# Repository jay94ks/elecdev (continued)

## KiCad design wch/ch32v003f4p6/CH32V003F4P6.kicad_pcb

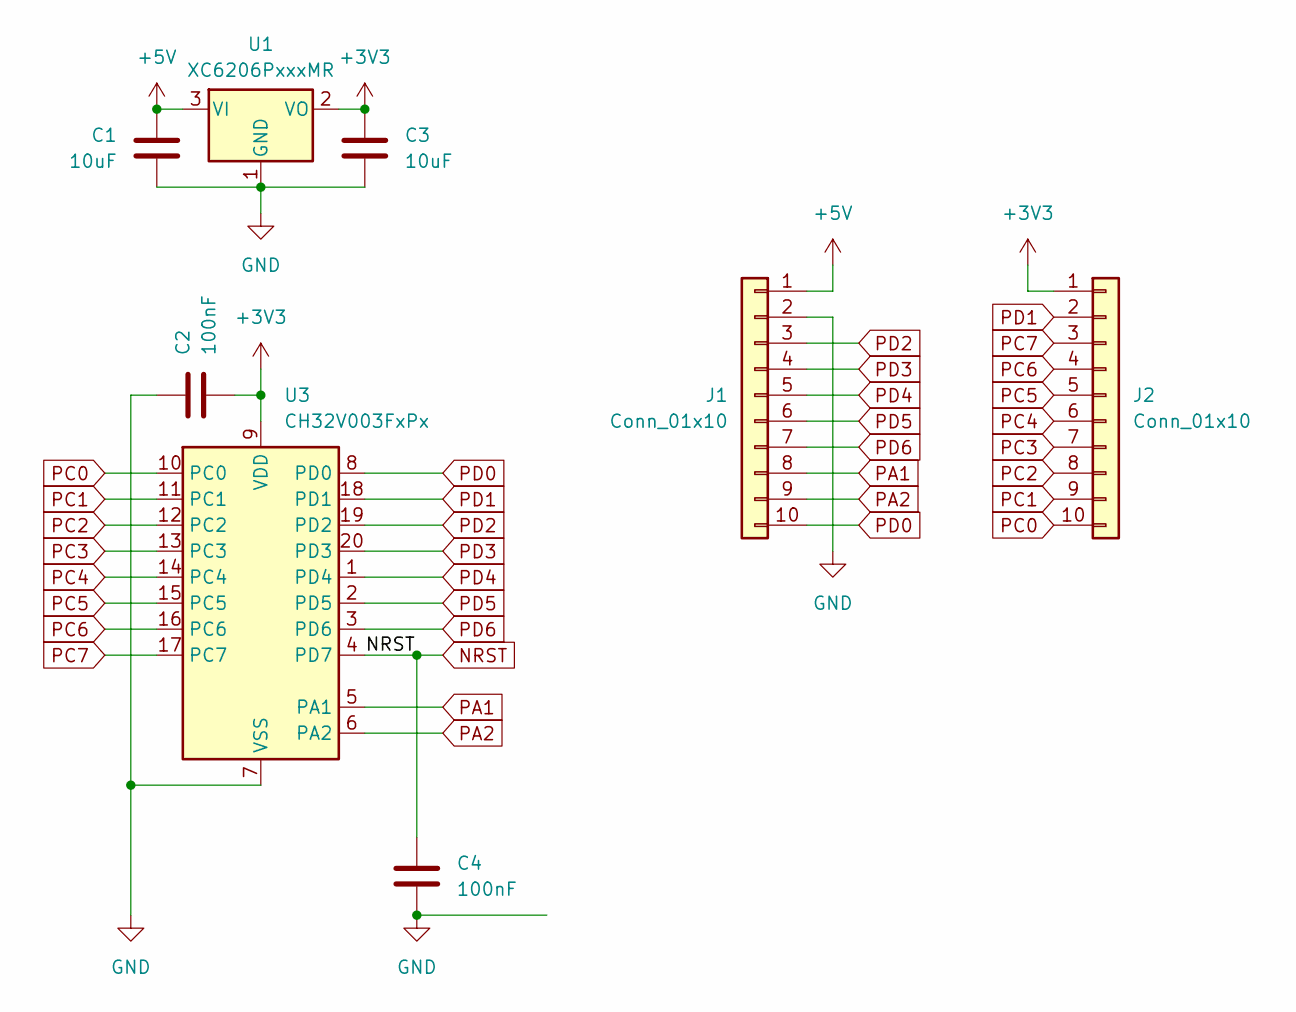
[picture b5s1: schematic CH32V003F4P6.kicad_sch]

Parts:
C1, C3: 10uF; C_0603_1608Metric
C2, C4: 100nF; C_0603_1608Metric
J1, J2: Conn_01x10; PinHeader_1x10_P2.54mm_Vertical
U1: XC6206PxxxMR; SOT-23-3
U3: CH32V003FxPx; TSSOP-20_4.4x6.5mm_P0.65mm

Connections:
+3V3: C2.2, C3.1, J2.1, U1.2 (VO), U3.9 (VDD)
+5V: C1.1, J1.1, U1.3 (VI)
GND: C1.2, C2.1, C3.2, C4.2, J1.2, U1.1 (GND), U3.7 (VSS)
NRST: C4.1, U3.4 (PD7)
PA1: J1.8, U3.5 (PA1)
PA2: J1.9, U3.6 (PA2)
PC0: J2.10, U3.10 (PC0)
PC1: J2.9, U3.11 (PC1)
PC2: J2.8, U3.12 (PC2)
PC3: J2.7, U3.13 (PC3)
PC4: J2.6, U3.14 (PC4)
PC5: J2.5, U3.15 (PC5)
PC6: J2.4, U3.16 (PC6)
PC7: J2.3, U3.17 (PC7)
PD0: J1.10, U3.8 (PD0)
PD1: J2.2, U3.18 (PD1)
PD2: J1.3, U3.19 (PD2)
PD3: J1.4, U3.20 (PD3)
PD4: J1.5, U3.1 (PD4)
PD5: J1.6, U3.2 (PD5)
PD6: J1.7, U3.3 (PD6)

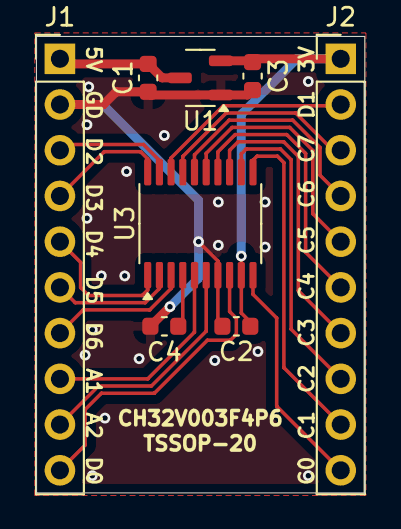
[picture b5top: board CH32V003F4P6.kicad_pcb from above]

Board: 2 copper layers, 18.2 x 25.4 mm, 8 parts (0 on the bottom side), 21 nets.

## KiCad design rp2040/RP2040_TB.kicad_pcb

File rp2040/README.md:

# RP2040.
ARM® Cortex®-M0+ Dual-core, 32bit, QFN-56.<br />
Features: 133 MHz max, 256kB SRAM, `UART` x2, `SPI` x2, `I2C` x2, `PWM` x 16 channel.<br/>
Board Size: -.<br />
Price: about -.

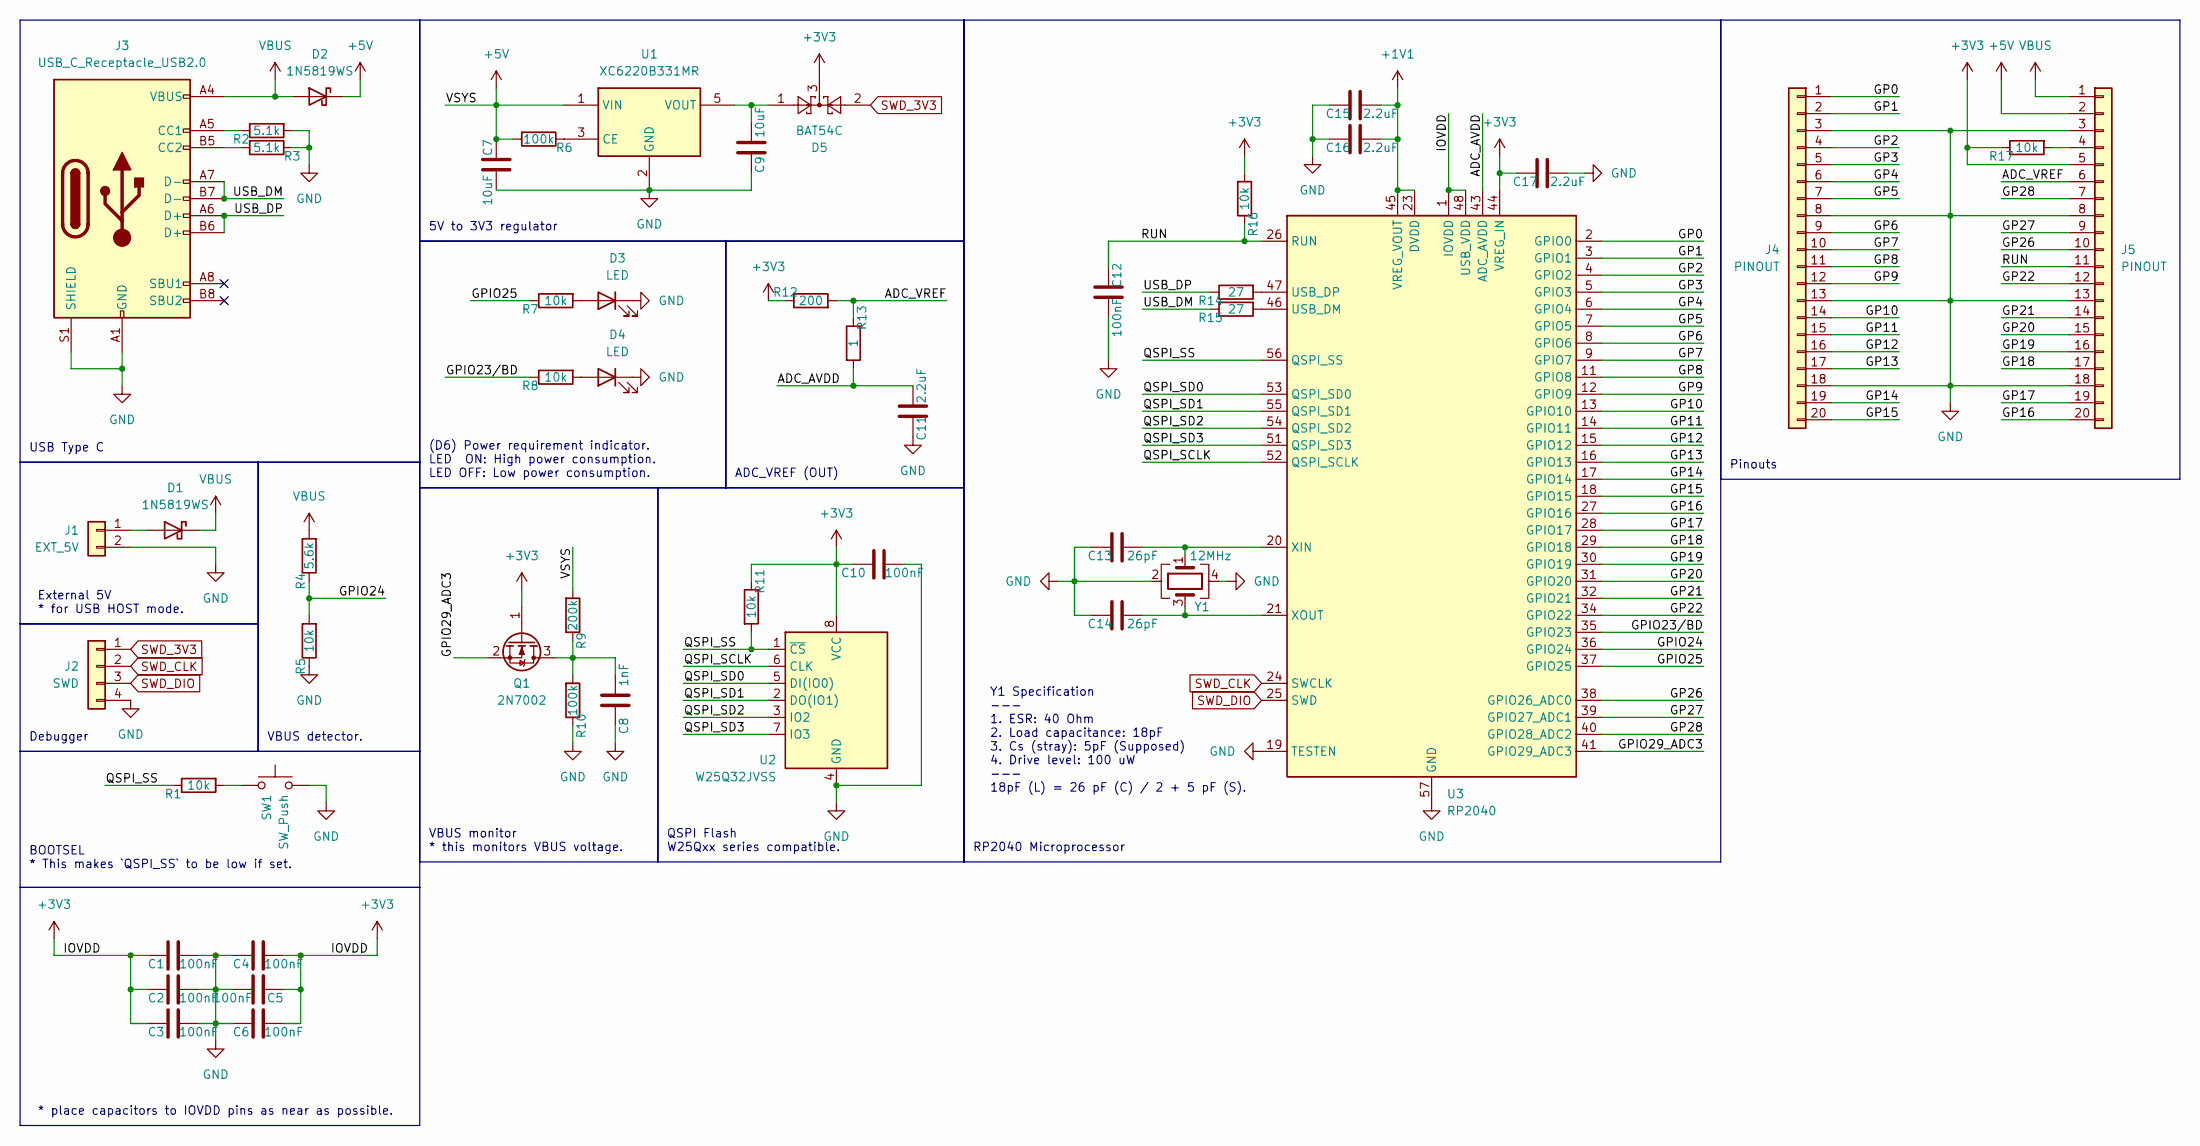
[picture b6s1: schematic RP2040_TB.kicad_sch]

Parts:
C1, C2, C3, C4, C5, C6, C10, C12: 100nF; C_0603_1608Metric
C7, C9: 10uF; C_0603_1608Metric
C8: 1nF; C_0603_1608Metric
C11, C15, C16, C17: 2.2uF; C_0603_1608Metric
C13, C14: 26pF; C_0603_1608Metric
D1, D2: 1N5819WS; D_SOD-323
D3, D4: LED; LED_0603_1608Metric
D5: BAT54C; SOT-23
J1: EXT_5V; PinHeader_1x02_P2.54mm_Vertical
J2: SWD; PinHeader_1x04_P2.54mm_Vertical
J3: USB_C_Receptacle_USB2.0; USB_C_Receptacle_Palconn_UTC16-G
J4, J5: PINOUT; PinHeader_1x20_P2.54mm_Vertical
Q1: 2N7002; SOT-23
R1, R5, R7, R8, R11, R16, R17: 10k; R_0603_1608Metric
R2, R3: 5.1k; R_0603_1608Metric
R4: 5.6k; R_0603_1608Metric
R6, R10: 100k; R_0603_1608Metric
R9: 200k; R_0603_1608Metric
R12: 200; R_0603_1608Metric
R13: 1; R_0603_1608Metric
R14, R15: 27; R_0603_1608Metric
SW1: SW_Push; SW_Push_SPST_NO_Alps_SKRK
U1: XC6220B331MR; SOT-23-5
U2: W25Q32JVSS; SOIC-8_5.23x5.23mm_P1.27mm
U3: RP2040; QFN-56-1EP_7x7mm_P0.4mm_EP3.2x3.2mm
Y1: 12MHz; Crystal_SMD_3225-4Pin_3.2x2.5mm

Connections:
+1V1: C15.2, C16.2, U3.23 (DVDD), U3.45 (VREG_VOUT), U3.50 (DVDD)
+3V3: C1.1, C2.1, C3.1, C4.1, C5.1, C6.1, C10.1, C17.1, D5.3, J5.5, Q1.1 (G), R11.1, R12.1, R16.2, R17.1, U2.8 (VCC), U3.1 (IOVDD), U3.10 (IOVDD), U3.22 (IOVDD), U3.33 (IOVDD), U3.42 (IOVDD), U3.44 (VREG_IN), U3.48 (USB_VDD), U3.49 (IOVDD)
+5V: C7.1, D2.1 (K), J5.2, R6.2, R9.2, U1.1 (VIN)
/ADC_AVDD: C11.2, R13.2, U3.43 (ADC_AVDD)
/ADC_VREF: J5.6, R12.2, R13.1
/GP0: J4.1, U3.2 (GPIO0)
/GP1: J4.2, U3.3 (GPIO1)
/GP2: J4.4, U3.4 (GPIO2)
/GP3: J4.5, U3.5 (GPIO3)
/GP4: J4.6, U3.6 (GPIO4)
/GP5: J4.7, U3.7 (GPIO5)
/GP6: J4.9, U3.8 (GPIO6)
/GP7: J4.10, U3.9 (GPIO7)
/GP8: J4.11, U3.11 (GPIO8)
/GP9: J4.12, U3.12 (GPIO9)
/GP10: J4.14, U3.13 (GPIO10)
/GP11: J4.15, U3.14 (GPIO11)
/GP12: J4.16, U3.15 (GPIO12)
/GP13: J4.17, U3.16 (GPIO13)
/GP14: J4.19, U3.17 (GPIO14)
/GP15: J4.20, U3.18 (GPIO15)
/GP16: J5.20, U3.27 (GPIO16)
/GP17: J5.19, U3.28 (GPIO17)
/GP18: J5.17, U3.29 (GPIO18)
/GP19: J5.16, U3.30 (GPIO19)
/GP20: J5.15, U3.31 (GPIO20)
/GP21: J5.14, U3.32 (GPIO21)
/GP22: J5.12, U3.34 (GPIO22)
/GP26: J5.10, U3.38 (GPIO26_ADC0)
/GP27: J5.9, U3.39 (GPIO27_ADC1)
/GP28: J5.7, U3.40 (GPIO28_ADC2)
/GPIO23/BD: R8.1, U3.35 (GPIO23)
/GPIO24: R4.1, R5.2, U3.36 (GPIO24)
/GPIO25: R7.1, U3.37 (GPIO25)
/GPIO29_ADC3: Q1.2 (S), U3.41 (GPIO29_ADC3)
/QSPI_SCLK: U2.6 (CLK), U3.52 (QSPI_SCLK)
/QSPI_SD0: U2.5 (DI(IO0)), U3.53 (QSPI_SD0)
/QSPI_SD1: U2.2 (DO(IO1)), U3.55 (QSPI_SD1)
/QSPI_SD2: U2.3 (IO2), U3.54 (QSPI_SD2)
/QSPI_SD3: U2.7 (IO3), U3.51 (QSPI_SD3)
/QSPI_SS: R1.1, R11.2, U2.1 (~CS), U3.56 (QSPI_SS)
/RUN: C12.1, J5.11, R16.1, U3.26 (RUN)
/USB_DM: J3.A7 (D-), J3.B7 (D-), R15.1
/USB_DP: J3.A6 (D+), J3.B6 (D+), R14.1
GND: C1.2, C2.2, C3.2, C4.2, C5.2, C6.2, C7.2, C8.1, C9.1, C10.2, C11.1, C12.2, C13.1, C14.1, C15.1, C16.1, C17.2, D3.1 (K), D4.1 (K), J1.2, J2.4, J3.A1 (GND), J3.A12 (GND), J3.B1 (GND), J3.B12 (GND), J3.S1 (SHIELD), J4.3, J4.8, J4.13, J4.18, J5.3, J5.8, J5.13, J5.18, R2.2, R3.1, R5.1, R10.1, SW1.1, U1.2 (GND), U2.4 (GND), U3.19 (TESTEN), U3.57 (GND), Y1.2, Y1.4
unnamed: D1.2 (A), J1.1
unnamed: D3.2 (A), R7.2
unnamed: D4.2 (A), R8.2
unnamed: J3.A5 (CC1), R2.1
unnamed: J3.B5 (CC2), R3.2
unnamed: J5.4, R17.2
unnamed: C8.2, Q1.3 (D), R9.1, R10.2
unnamed: R1.2, SW1.2
unnamed: R6.1, U1.3 (CE)
unnamed: C9.2, D5.1, U1.5 (VOUT)
unnamed: R15.2, U3.46 (USB_DM)
unnamed: R14.2, U3.47 (USB_DP)
unnamed: C13.2, U3.20 (XIN), Y1.1
unnamed: C14.2, U3.21 (XOUT), Y1.3
SWD_3V3: D5.2, J2.1
SWD_CLK: J2.2, U3.24 (SWCLK)
SWD_DIO: J2.3, U3.25 (SWD)
VBUS: D1.1 (K), D2.2 (A), J3.A4 (VBUS), J3.A9 (VBUS), J3.B4 (VBUS), J3.B9 (VBUS), J5.1, R4.2

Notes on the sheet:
VBUS monitor * this monitors VBUS voltage.
VBUS detector.
ADC_VREF (OUT)
External 5V * for USB HOST mode.
Pinouts
Y1 Specification --- 1. ESR: 40 Ohm 2. Load capacitance: 18pF 3. Cs (stray): 5pF (Supposed) 4. Drive level: 100 uW --- 18pF (L) = 26 pF (C) / 2 + 5 pF (S).
Debugger
RP2040 Microprocessor
QSPI Flash W25Qxx series compatible.
(D6) Power requirement indicator. LED ON: High power consumption. LED OFF: Low power consumption.
USB Type C
* place capacitors to IOVDD pins as near as possible.
BOOTSEL * This makes `QSPI_SS` to be low if set.
5V to 3V3 regulator

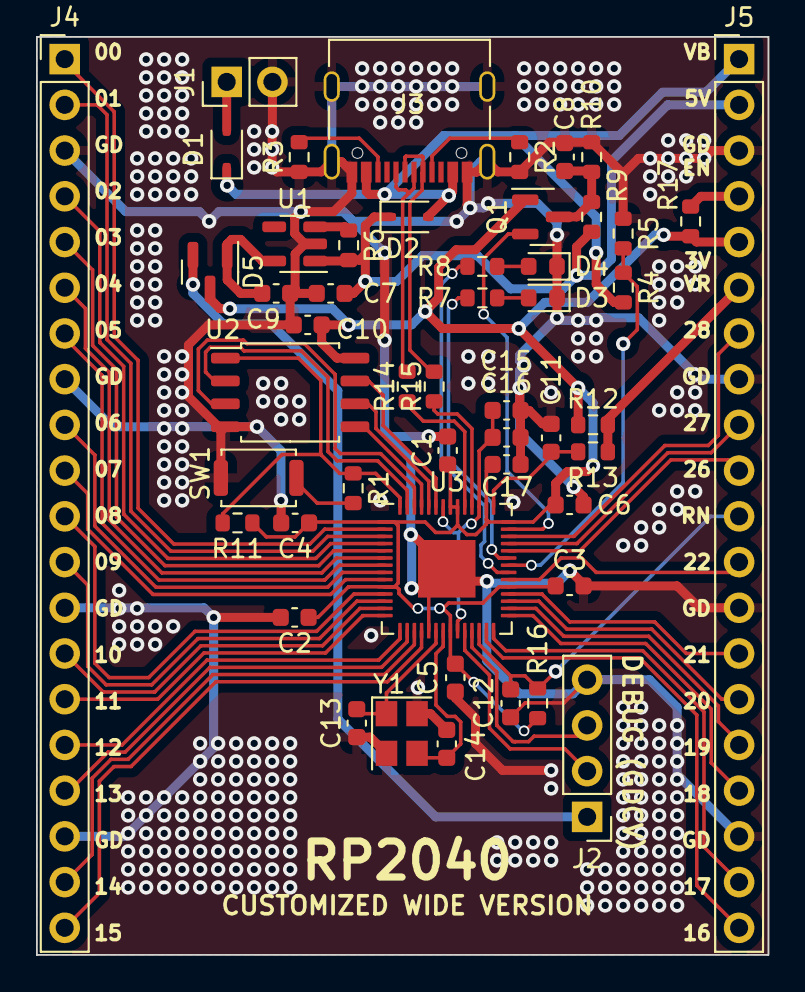
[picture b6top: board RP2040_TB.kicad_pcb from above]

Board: 2 copper layers, 40.6 x 51.0 mm, 50 parts (0 on the bottom side), 63 nets.

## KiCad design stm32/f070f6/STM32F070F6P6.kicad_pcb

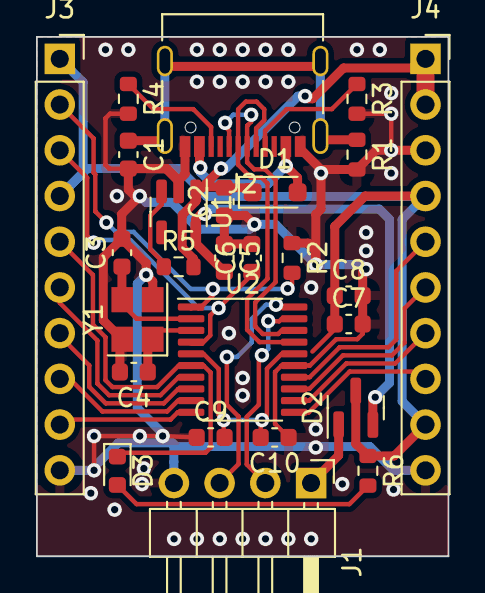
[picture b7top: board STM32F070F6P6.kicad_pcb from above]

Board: 2 copper layers, 22.9 x 28.9 mm, 26 parts (0 on the bottom side), 28 nets.

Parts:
C1: 4.7nF; C_0603_1608Metric
C2, C5: 10uF; C_0603_1608Metric
C3, C4: 8pF; C_0603_1608Metric
C6, C7, C9: 100nF; C_0603_1608Metric
C8: 4.7uF; C_0603_1608Metric
C10: 1uF; C_0603_1608Metric
D1: 1N5819WS; D_SOD-323_HandSoldering
D2: BAT54C-KL3; SOT-23
D3: LED; LED_0603_1608Metric
J1: STLINK; PinHeader_1x04_P2.54mm_Horizontal
J2: USB_C_REC_16PIN; USB_C_Receptacle_Palconn_UTC16-G
J3, J4: L; PinSocket_1x10_P2.54mm_Vertical
R1: 56k; R_0603_1608Metric
R2: 10k; R_0603_1608Metric
R3, R4: 5.1k; R_0603_1608Metric
R5: 100k; R_0603_1608Metric
R6: 1k; R_0603_1608Metric
U1: XC6220B331MR; SOT-23-5
U2: STM32F070F6Px; TSSOP-20_4.4x6.5mm_P0.65mm
Y1: 8 MHz; Crystal_SMD_3225-4Pin_3.2x2.5mm

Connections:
+3.3V: C7.1, C8.1, C9.2, C10.2, D2.3, J3.1, J3.4, J4.4, J4.9, R6.1, U2.5 (VDDA), U2.16 (VDD)
+3.3VA: C5.2, D2.2, U1.5 (VOUT)
+5V: C2.2, D1.1 (K), J4.1, J4.2, R5.2, U1.1 (VIN)
BOOT0: J3.2, R2.2, U2.1 (BOOT0)
GND: C1.2, C2.1, C3.2, C4.2, C5.1, C6.2, C7.2, C8.2, C9.1, C10.1, J1.4, J2.A1 (GND), J2.A12 (GND), J2.B1 (GND), J2.B12 (GND), J3.10, J4.3, J4.10, R1.2, R2.1, R3.2, R4.2, U1.2 (GND), U2.15 (VSS), Y1.2, Y1.4
HSE_IN: C3.1, U2.2 (PF0), Y1.3
HSE_OUT: C4.1, U2.3 (PF1), Y1.1
NRST: C6.1, J3.3, U2.4 (NRST)
unnamed: D1.2 (A), J2.A4 (VBUS), J2.A9 (VBUS), J2.B4 (VBUS), J2.B9 (VBUS)
unnamed: D3.2 (A), R6.2
unnamed: D2.1, J1.1
unnamed: J2.A5 (CC1), R3.1
unnamed: J2.B5 (CC2), R4.1
unnamed: C1.1, J2.S1 (SHIELD), R1.1
unnamed: R5.1, U1.3 (CE)
PA0: D3.1 (K), J3.5, U2.6 (PA0)
PA1: J3.6, U2.7 (PA1)
PA2: J3.7, U2.8 (PA2)
PA3: J3.8, U2.9 (PA3)
PA4: J3.9, U2.10 (PA4)
PA5: J4.8, U2.11 (PA5)
PA6: J4.7, U2.12 (PA6)
PA7: J4.6, U2.13 (PA7)
PB1: J4.5, U2.14 (PB1)
SWCLK: J1.3, U2.20 (PA14)
SWDIO: J1.2, U2.19 (PA13)
USB_DM: J2.A7 (D-), J2.B7 (D-), U2.17 (PA9/PA11)
USB_DP: J2.A6 (D+), J2.B6 (D+), U2.18 (PA10/PA12)

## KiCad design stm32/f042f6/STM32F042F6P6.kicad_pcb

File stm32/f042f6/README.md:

# STM32 F042F6Px
ARM® Cortex®-M0, 32bit, TSOC-20.<br />
Features: 48 MHz MAX, 32K Flash, 6K RAM, `USART`, `SPI`, `USB FS`, `CAN`, `I2C`.<br/>
Board Size: 22.86 mm * 25.45 mm.<br />
Price: about 5,500 KRW, 4.15 USD.

### Gerber files.
Download: https://github.com/jay94ks/elecdev/blob/main/stm32/f042f6/STM32F042F6Px_v1_1.zip

## Schematic.
* C3, C4: 8pF -> 32pF. (IMPORTANT)

## Board Rendering.

## Artwork.
### Top side

### Bottom side

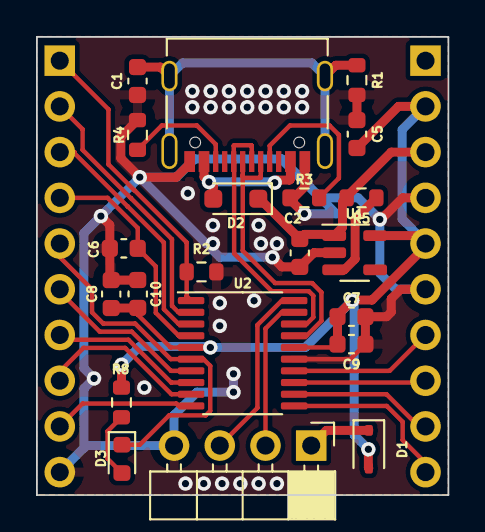
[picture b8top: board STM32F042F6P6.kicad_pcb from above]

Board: 2 copper layers, 22.9 x 25.5 mm, 23 parts (0 on the bottom side), 27 nets.

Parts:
C1: 4.7nF; C_0603_1608Metric
C2, C5: 10uF; C_0603_1608Metric
C6, C7, C9: 100nF; C_0603_1608Metric
C8: 4.7uF; C_0603_1608Metric
C10: 1uF; C_0603_1608Metric
D1: 1N5819WS; D_SOD-323
D2: 1N5819WS; D_SOD-323_HandSoldering
D3: LED; LED_0603_1608Metric
J1: USB_C_REC_16PIN; USB_C_Receptacle_Palconn_UTC16-G
J2: STLINK; PinHeader_1x04_P2.54mm_Horizontal
J3: L; PinHeader_1x10_P2.54mm_Vertical
J4: R; PinHeader_1x10_P2.54mm_Vertical
R1: 56k; R_0603_1608Metric
R2: 10k; R_0603_1608Metric
R3, R4: 5.1k; R_0603_1608Metric
R5: 100k; R_0603_1608Metric
R8: 1k; R_0603_1608Metric
U1: XC6220B331MR; SOT-23-5
U2: STM32F042F6Px; TSSOP-20_4.4x6.5mm_P0.65mm

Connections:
+3.3V: C5.2, C7.1, C8.1, C9.2, C10.2, D1.2 (A), J4.2, J4.5, R8.1, U1.5 (VOUT), U2.5 (VDDA), U2.16 (VDD)
+5V: C2.2, D2.1 (K), J4.1, J4.3, R5.2, U1.1 (VIN)
GND: C1.2, C2.1, C5.1, C6.2, C7.2, C8.2, C9.1, C10.1, J1.A1 (GND), J1.A12 (GND), J1.B1 (GND), J1.B12 (GND), J2.4, J3.10, J4.4, J4.6, R1.2, R2.1, R3.2, R4.2, U1.2 (GND), U2.15 (VSSA)
NRST: C6.1, J3.4, U2.4 (NRST)
unnamed: D1.1 (K), J2.1
unnamed: D2.2 (A), J1.A4 (VBUS), J1.A9 (VBUS), J1.B4 (VBUS), J1.B9 (VBUS)
unnamed: D3.2 (A), R8.2
unnamed: J1.A5 (CC1), R3.1
unnamed: J1.B5 (CC2), R4.1
unnamed: C1.1, J1.S1 (SHIELD), R1.1
unnamed: R5.1, U1.3 (CE)
PA0: D3.1 (K), J3.5, U2.6 (PA0)
PA1: J3.6, U2.7 (PA1)
PA2: J3.7, U2.8 (PA2)
PA3: J3.8, U2.9 (PA3)
PA4: J3.9, U2.10 (PA4)
PA5: J4.10, U2.11 (PA5)
PA6: J4.9, U2.12 (PA6)
PA7: J4.8, U2.13 (PA7)
PB1: J4.7, U2.14 (PB1)
PB8/BOOT0: J3.1, R2.2, U2.1 (PB8)
PF0/HSE_IN: J3.2, U2.2 (PF0)
PF1/HSE_OUT: J3.3, U2.3 (PF1)
SWCLK: J2.3, U2.20 (PA14)
SWDIO: J2.2, U2.19 (PA13)
USB_DM: J1.A7 (D-), J1.B7 (D-), U2.17 (PA9/PA11)
USB_DP: J1.A6 (D+), J1.B6 (D+), U2.18 (PA10/PA12)

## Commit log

2023-11-13 Update `README.md`
2023-11-13 Update README.md and mistyped capacitor size correction.
2023-11-13 USB_C_BREAKOUT
2023-11-19 WIP: F070F6P6, Fix: Diode direction corrected for F042F6P6.
2023-11-20 Fix: Diode direction corrected.
2023-11-20 Changed `9-Pin` header to 8 pin header.
2023-11-20 Update: Artwork completed for `F070F6P6`.
2023-11-23 F042: HSE crystal removal because it didn't be needed.
2023-11-23 F042 tested.
2023-11-23 Erased component listing. See KiCAD's BOM list.
2023-11-27 Update 2023-11-27
2023-11-27 Rename~
2023-11-30 `F042` board completed
2024-03-21 RP2040
2024-06-27 New boards
2024-08-24 CH32X035G8U8
2024-09-08 STM32F107RBT6
2024-09-08 added images
